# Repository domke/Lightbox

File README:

Work in Progress. Not yet working.

In the meantime have a look at https://github.com/C3MA/Lightbox

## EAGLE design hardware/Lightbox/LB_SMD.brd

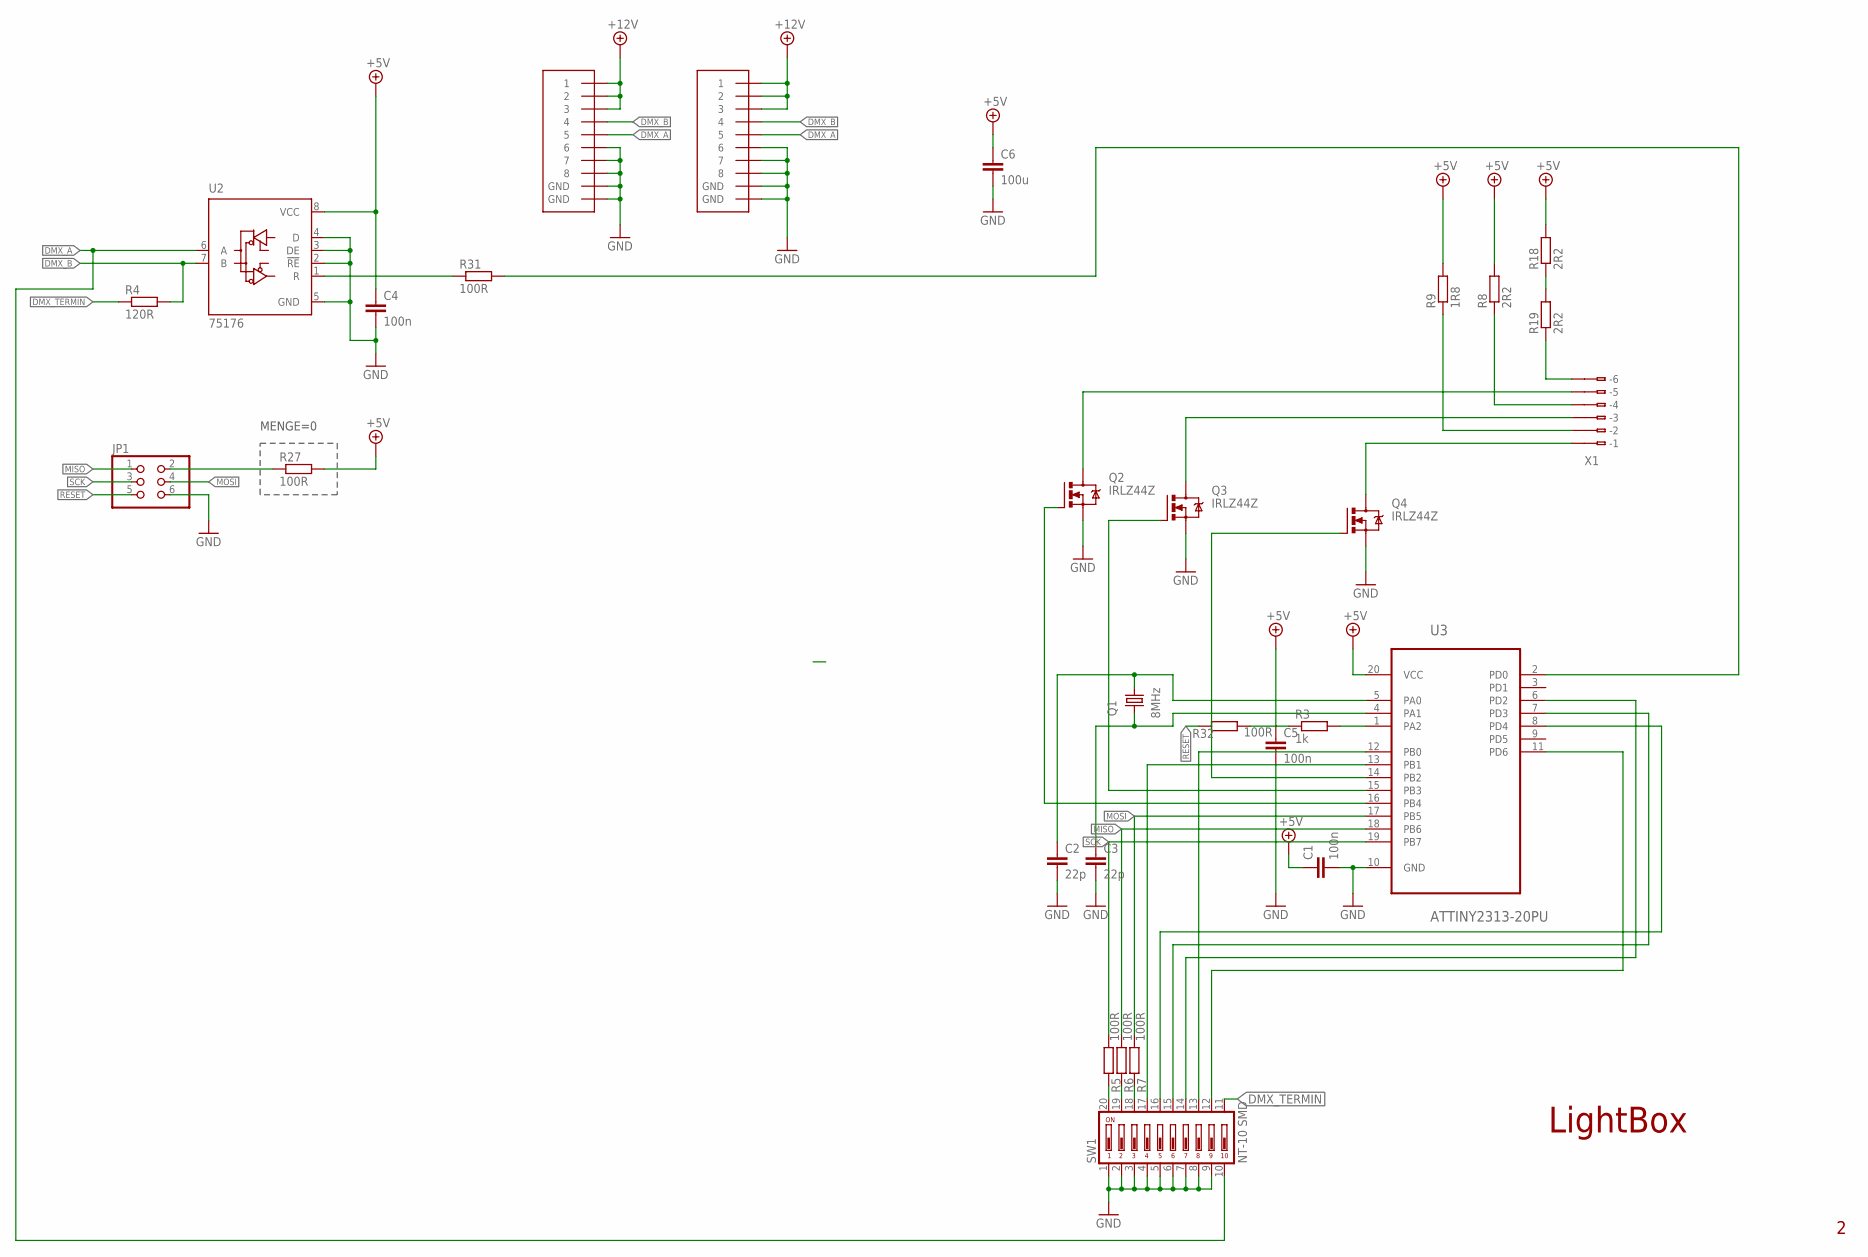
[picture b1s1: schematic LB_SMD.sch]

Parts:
C1, C4, C5: 100n; C0805
C2, C3: 22p; C0805
C6: 100u; C0805
JP1: PINHD-2X3; 2X03
Q1: 8MHz; HC49/S
Q2, Q3, Q4: IRLZ44Z; TO220BH
R3: 1k; R0805
R4: 120R; R0805
R5, R6, R7, R31, R32: 100R; R0805
R8, R18, R19: 2R2; 0207/7
R9: 1R8; 0207/7
R27: 100R; R1206
SW1: NT-10 SMD; CTS-219-10
U2: 75176; D_R-PDSO-G8
U3: ATTINY2313-20PU; DIP254P762X533-20
U$1, U$2: MEBP8-8G; RJ45-REICHELT
X1: 233-506

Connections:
+5V: C1.1, C4.1, C6.1, R3.1, R8.2, R9.2, R18.2, R27.2, U2.8 (VCC), U3.20 (VCC)
+12V: U$1.1, U$1.2, U$1.3, U$2.1, U$2.2, U$2.3
DMX_A: SW1.10, U2.6 (A), U$1.5, U$2.5
DMX_B: R4.2, U2.7 (B), U$1.4, U$2.4
DMX_TERMIN: R4.1, SW1.11
GND: C1.2, C2.2, C3.2, C4.2, C5.2, C6.2, JP1.6, Q2.S, Q3.S, Q4.S, SW1.1, SW1.2, SW1.3, SW1.4, SW1.5, SW1.6, SW1.7, SW1.8, SW1.9, U2.2 (!RE), U2.3 (DE), U2.4 (D), U2.5 (GND), U3.10 (GND), U$1.6, U$1.7, U$1.8, U$1.GND@1 (GND), U$1.GND@2 (GND), U$2.6, U$2.7, U$2.8, U$2.GND@1 (GND), U$2.GND@2 (GND)
MISO: JP1.1, R6.2, U3.18 (PB6)
MOSI: JP1.4, R7.2, U3.17 (PB5)
unnamed: R3.2, U3.1 (PA2)
unnamed: SW1.12, U3.11 (PD6)
unnamed: SW1.13, U3.12 (PB0)
unnamed: R31.1, U2.1 (R)
unnamed: C5.1, R32.2
unnamed: JP1.2, R27.1
unnamed: R5.1, SW1.20
unnamed: R6.1, SW1.19
unnamed: R7.1, SW1.18
unnamed: Q3.G, U3.15 (PB3)
unnamed: R18.1, R19.2
unnamed: SW1.17, U3.13 (PB1)
unnamed: SW1.16, U3.8 (PD4)
unnamed: SW1.15, U3.7 (PD3)
unnamed: SW1.14, U3.6 (PD2)
unnamed: Q4.G, U3.14 (PB2)
unnamed: Q4.D, X1.B1 (B-1)
unnamed: Q3.D, X1.B3 (B-3)
unnamed: Q2.D, X1.B5 (B-5)
unnamed: R19.1, X1.B6 (B-6)
unnamed: R8.1, X1.B4 (B-4)
unnamed: R9.1, X1.B2 (B-2)
unnamed: Q2.G, U3.16 (PB4)
unnamed: C2.1, Q1.1, U3.5 (PA0)
unnamed: C3.1, Q1.2, U3.4 (PA1)
RESET: JP1.5, R32.1
SCK: JP1.3, R5.2, U3.19 (PB7)

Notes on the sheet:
LightBox
MENGE=0

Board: 2 copper layers, 29 parts (0 on the bottom side), 35 nets, no tracks yet.

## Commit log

2012-12-20 started conversion to mosfet-design
2012-12-20 removed parts of old routing from PCB
2013-01-20 changes towards THT layout
